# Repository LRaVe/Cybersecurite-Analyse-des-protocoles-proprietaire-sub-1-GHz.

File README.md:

# Projet 2A -  Cybersecurite-Analyse-des-protocoles-proprietaire-sub-1-GHz

## Description du Projet
Bienvenue sur le dépôt GitHub de notre projet de cybersécurité, réalisé dans le cadre de notre projet de deuxième année. Ce projet repose sur l'utilisation du flipper zero, et ensuite de le reproduire avec une STM32WL55.

## Équipe du Projet
Nous sommes une équipe de cinq étudiants :

- **Lucas Raveloarinoro**
- **Hevisinda Top**
- **Wassim Makni**
- **Awa Fofana**
- **Elhoussaine Assanfe**

## Objectifs : 4 Démonstrations et une application

Démo A : Flipper Zero — attaque simple (sans chiffrement) sur la sonnette.

Démo B : Flipper Zero — tentative d’attaque sur la clé de voiture (rolling‑code).

Démo C : STM32WL55 — reproduction de l’attaque simple (sonnette).

Démo D : STM32WL55 — expérimentation et analyse du rolling‑code (clé de voiture).

- La création d’une application sur Flipper capable passivement d’écouter les communications, et en déduire les faiblesses de sécurités des appareils écoutés.

## Organisation du Projet

Afin d’assurer une conduite de projet structurée et efficace, plusieurs outils de planification, de suivi et de conception ont été utilisés tout au long du projet. Ces documents ont permis de clarifier les objectifs, de répartir les tâches et de suivre l’avancement des travaux.

### Planning et gestion du temps
- [Gantt](Organisation/Gantt.png) : planification des différentes phases du projet.  
- [Roadmap](Organisation/Roadmap.png) : suivi de l’avancement au sein de l’équipe.

### Conception et spécification
- [Diagramme des exigences](Organisation/Diagramme_des_Exigences.png) : définition des besoins fonctionnels et techniques du projet.  
- [Cahier des charges](Organisation/Cahier_Des_charges.png) : description des objectifs.

### RSE et Durabilité

Dans le cadre de ce projet, nous avons mené une réflexion sur des thématiques **environnementales et sociétales** :  

- **Durabilité des composants** : nous avons choisi des composants durables et à longue durée de vie pour réduire l’impact environnemental.  
- **Économie d’énergie** : les dispositifs peuvent fonctionner en mode basse consommation afin de limiter la consommation globale.  
- **Impact sociétal** : en analysant les protocoles Sub‑GHz, nous avons également pris en compte l’aspect sécurité et confidentialité des communications.

Ces critères sont **formalisés dans le [Cahier des charges](Organisation/Cahier_Des_charges.png)** et représentés dans le **[Diagramme des exigences](Organisation/Diagramme_des_Exigences.png)**.

## Sous-Projet FlipperZero Application

Rappel Objectif : utiliser les composants inclus dans le FlipperZero pour reconsrtruire du début une application de capture et de relecture de signaux sub-GHz.

### Avancée Dec. 2025 

L'application parvient à récupérer des paquets envoyés de fréquence $\textbf{433.92\~ MHz}$. Il ne manque maintenant que la partie relecture, même s'il est possible de le récupérer directement dans les fichiers du flipper.

### Avancée Jan. 2026 - Application Fonctionnelle ✅

L'application est maintenant **complètement fonctionnelle** avec capture et replay de signaux radio.

#### Architecture de l'Application

```
┌─────────────────────────────────────────────────────────────┐
│                    APPLICATION SUBGHZ                       │
├─────────────────────────────────────────────────────────────┤
│  CAPTURE (app_state=0)                                      │
│  └── furi_hal_subghz_start_async_rx() → capture_callback()  │
│      └── Filtrage du bruit → Stockage dans raw_buffer[]     │
│                                                             │
│  AFFICHAGE (app_state=1)                                    │
│  └── Lecture du fichier .sub sauvegardé                     │
│                                                             │
│  REPLAY (app_state=2)                                       │
│  └── Transmission manuelle TX/IDLE avec timings précis      │
└─────────────────────────────────────────────────────────────┘
```

#### APIs Flipper Zero Utilisées

| API | Fonction |
|-----|----------|
| `furi_hal_subghz_*` | Contrôle du module radio CC1101 (433.92 MHz) |
| `furi_hal_subghz_start_async_rx()` | Démarrage de la capture asynchrone |
| `furi_hal_subghz_tx()` / `furi_hal_subghz_idle()` | Émission/arrêt pour le replay |
| `furi_thread_*` | Threads pour capture/replay non-bloquants |
| `storage_*` / `stream_*` | Lecture/écriture fichiers .sub sur SD |
| `gui_*` / `canvas_*` | Interface utilisateur |

#### Problèmes Rencontrés et Solutions

##### 1. Capture de bruit en permanence
**Problème** : L'antenne capte énormément de bruit électromagnétique ambiant, rendant impossible la distinction d'un vrai signal.

**Solution** : Filtrage multi-niveaux dans `capture_callback()` :
```c
// Ignorer les durées < 150µs (bruit haute fréquence)
if(duration < 150) return;

// Ignorer les durées > 20ms (silence/pause)
if(duration > 20000) return;

// Attendre 30 impulsions valides consécutives avant d'enregistrer
if(consecutive_pulses < 30) return;
```

##### 2. API `subghz_devices` non fonctionnelle
**Problème** : L'API `subghz_devices` (plus récente) causait des blocages - l'appareil ne trouvait pas le device radio.

**Solution** : Utilisation de l'API bas niveau `furi_hal_subghz` qui fonctionne directement avec le CC1101 :
```c
furi_hal_subghz_reset();
furi_hal_subghz_idle();
furi_hal_subghz_load_custom_preset(subghz_device_cc1101_preset_ook_650khz_async_regs);
furi_hal_subghz_set_frequency_and_path(433920000);
```

##### 3. Crash lors du replay avec `async_tx`
**Problème** : L'utilisation de `furi_hal_subghz_start_async_tx()` avec un callback provoquait des crashes (contexte d'interruption incompatible avec certaines fonctions).

**Solution** : Transmission manuelle en alternant `tx()` et `idle()` avec des délais précis :
```c
for(size_t i = 0; i < tx_buffer_size; i++) {
    if(timing > 0) {
        furi_hal_subghz_tx();      // Émet
    } else {
        furi_hal_subghz_idle();    // Silence
    }
    furi_delay_us(abs(timing));    // Attend la durée exacte
}
```

##### 4. UI bloquée sur "ENVOI EN COURS"
**Problème** : Après la transmission, l'écran restait bloqué et n'affichait jamais "TERMINÉ".

**Cause** : L'appel `furi_hal_subghz_sleep()` bloquait indéfiniment le thread.

**Solution** : Suppression de `furi_hal_subghz_sleep()` - la radio reste en mode `idle` ce qui est suffisant.

##### 5. Synchronisation des flags entre threads
**Problème** : Les variables `is_replaying` et `replay_finished` n'étaient pas toujours visibles entre le thread de replay et le thread principal (UI).

**Solution** : Utilisation de `volatile` pour les variables partagées :
```c
volatile bool is_replaying;
volatile bool replay_finished;
```

#### Format du Fichier .sub

```
Filetype: Flipper SubGhz RAW File
Version: 1
Frequency: 433920000
Preset: FuriHalSubGhzPresetOok650Async
Protocol: RAW
RAW_Data: 1001 -352 379 -986 353 -10750 385 -954 999 -350 ...
RAW_Data: 379 -966 1007 -366 987 -368 987 -366 353 -984 ...
```

- **Valeurs positives** : durée HIGH (émission) en µs
- **Valeurs négatives** : durée LOW (silence) en µs

## Sous-Projet STM32

### Objectif

L’objectif de ce sous‑projet est de reproduire, à l’aide d’une carte STM32WL55JC2, le comportement radio observé avec le Flipper Zero.
Cette approche vise à mieux comprendre les communications Sub‑GHz et à évaluer les possibilités d’attaque sur des dispositifs simples, comme une sonnette sans fil à 433 MHz.

La STM32WL55 intègre un module de communciation radio Sub‑GHz, couramment utilisé dans des applications IoT à faible consommation (capteurs, télémétrie, réseaux longue portée). Elle supporte principalement les modulations LoRa et FSK.

### Mise en place de la communication Sub-GHz  
*(Adaptation de l'exemple PingPong)*

Dans un premier temps, une communication radio simple a été mise en place entre deux cartes STM32 à partir de l’exemple Ping‑Pong fourni par ST.
Une carte agit comme émetteur et envoie un message, tandis que l’autre joue le rôle de récepteur et renvoie une réponse. Cette méthode permet de valider le bon fonctionnement de la transmission et de la réception radio, ainsi que la stabilité de la liaison.

La communication a ensuite été contrôlée à l’aide des boutons présents sur les cartes.

Pour la carte correspondant au **Flipper Zero** :

- **Bouton 2** : envoi du signal radio stocké  
- **Bouton 1** : réception et stockage d’un signal radio  

Plusieurs scénarios ont été testés en alternant les rôles des cartes afin de vérifier que l’émission et la réception fonctionnent correctement dans les deux sens. Ces tests ont permis de confirmer que la communication Sub-GHz entre deux STM32 est opérationnelle avec les modulations supportées. 

Une fois cette étape validée, nous avons implémenté un schéma de fonctionnement proche de celui du Flipper Zero : une carte agit comme récepteur‑enregistreur du signal, tandis que la seconde assure l’émission contrôlée d’un signal de test.

### Schéma de principe

```text
┌──────────────────────────────┐      ┌────────────────────────────────┐
│  Carte STM32WL (Émetteur)    │      │  Carte STM32WL (Flipper Zero)   │
│        Carte Test            │<────>│                                │
│                              │      │                                │
│  ComPort <────────────────── │      │ ───────────────────> ComPort   │
└──────────────────────────────┘      └────────────────────────────────┘
```

### Tentative de hacking d’une sonnette 433 MHz

Dans un second temps, nous avons cherché à hacker une sonnette sans fil fonctionnant à 433 MHz, dans l’objectif de reproduire un cas d’attaque similaire à ceux réalisables avec le Flipper Zero. Bien que la fréquence utilisée par la sonnette soit identique à celle exploitée par la carte STM32, aucun signal exploitable n’a pu être reçu.

Cette limitation s’explique par une différence de modulation. La sonnette utilise une modulation de type **ASK/OOK**, tandis que le récepteur Sub-GHz intégré à la STM32 ne prend en charge que les modulations **LoRa** et **FSK**. Ainsi, même avec une fréquence porteuse identique, la modulation incompatible empêche toute réception ou décodage du signal.

### Limites de l’approche STM32

Cette expérimentation met en évidence une limite importante de notre approche : la fréquence seule ne suffit pas pour intercepter ou reproduire un signal radio. Le type de modulation joue un rôle déterminant dans la compatibilité des systèmes.

Contrairement au Flipper Zero, qui supporte un large éventail de modulations grâce à son transceiver dédié, la carte STM32 utilisée reste limitée aux modulations prévues par son matériel.

### PCB Interface homme-machine
Pour reproduire fidèlement le Flipper Zero, nous avons développé une carte PCB de type interface homme-machine (IHM),Prenant la forme d'un shield Arduino (R3) qui s'emboîte parfaitement sur notre carte Nucleo, elle intègre un écran OLED clair et deux boutons de navigation. C'est cette interface simple et robuste qui nous permet de contrôler manuellement l'application radio : capturer un signal, l'enregistrer, et de le retransmettre d'une simple pression. L'ensemble a été conçu pour être stable et fiable, avec une électronique adaptée, afin de se concentrer sur l'objectif du projet.

### Conclusion à mi-durée du sous-projet STM32

En conclusion, nous avons réussi à reproduire partiellement le comportement du Flipper Zero en mettant en place une communication Sub-GHz fonctionnelle entre deux cartes STM32. En revanche, le hacking de la sonnette 433 MHz n’a pas été possible en raison des contraintes matérielles liées aux modulations supportées, ce qui souligne l’importance du choix du transceiver dans les attaques radio Sub-GHz.

## Suite du projet : CaribouLite & Réseaux LoRa sécurisés

Afin de dépasser les limitations rencontrées avec la STM32WL55, nous avons poursuivi le projet en utilisant une plateforme radio beaucoup plus flexible : **CaribouLite sur Raspberry Pi**.  
Cette nouvelle étape nous a permis de revenir à l’écoute large bande Sub-GHz et d’élargir nos capacités d’analyse radio.

Grâce à CaribouLite, nous avons pu :

- observer le spectre radio Sub-GHz de manière plus fine  
- capturer et analyser différents signaux radio  
- confirmer expérimentalement les limites des attaques de replay  

L'étude se fait sur un réseau **Meshtastic**, un système de communication LoRa mesh open-source.

---

## Nouvel objectif : reproduction d’une attaque Man-in-the-Middle

L'objectif est de reproduire une **attaque Man-in-the-Middle (MITM)** sur un réseau radio LoRa.

Une attaque Man-in-the-Middle consiste pour un attaquant à s’interposer entre deux appareils qui communiquent sans qu’ils s’en rendent compte.

Dans ce scénario, l’attaquant peut :
- intercepter les messages échangés
- tenter d’en comprendre le contenu
- modifier les messages avant retransmission
- se faire passer pour l’un des participants

Communication normale :

Appareil A ─────────────► Appareil B

Communication sous attaque MITM :

Appareil A ───► Attaquant ───► Appareil B

Les deux appareils pensent communiquer directement, alors que toute la communication passe en réalité par l’attaquant.

---

La mise en place et les détails du projet sont disponibles dans le dossier :

[LoRa_Meshtastic](LoRa_Meshtastic/README.md)

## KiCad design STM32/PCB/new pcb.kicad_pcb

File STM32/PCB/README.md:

Ce projet consiste en la conception d'un shield au format Arduino R3 pour la carte STM32 Nucleo-WL55JC2. 
Il permet l'affichage d'informations sur un écran OLED et le contrôle manuel de fonctions de lecture/sauvegarde (Rx) et d'émission (Tx) via deux boutons poussoirs.
##  Spécifications Matérielles
Microcontrôleur cible : STM32 Nucleo-WL55JC2 (Logique $3.3 \text{ V}$).
Affichage : Écran OLED SSD1315 via connecteur J5 (7 pins).
Protocole d'affichage : SPI (plus rapide que l'I2C pour les animations).
Contrôles : 2x Boutons poussoirs tactiles avec résistances de rappel externes.
## Logique des Boutons (Active High)
Ce projet utilise des résistances Pull-Down externes pour garantir une immunité au bruit maximale et un signal stable, plus fiable de les configurées.

Composant >  S1 (Read), Valeur > N/A, Fonction > Déclenche la lecture (Rx),État au repos > LOW (0 V), État pressé > HIGH (3.3 V)

Composant >S2 (Send), Valeur > N/A, Fonction > Déclenche l'émission (Tx),État au repos > LOW (0 V), État pressé > HIGH (3.3 V)

Composant > "R1, R2", Valeur > 10 kΩ, Fonction > Résistances Pull-Down,État au repos > Maintenir le signal à 0 V, État pressé > N/A
## Alimentation
Le shield est alimenté par le rail $+3V3$ de la Nucleo.Les boutons tirent leur alimentation en parallèle de la ligne de l'écran OLED pour simplifier le routage.
> L'utilisation du $+5 \text{ V}$ est strictement interdite pour éviter d'endommager les GPIO du STM32.
## Brochage (Pinout)
Signal > BTN_RX (S1),Pin Shield (Arduino) > D2,Pin STM32 (Nucleo) > PA10

Signal > BTN_TX (S2),Pin Shield (Arduino) > D3,Pin STM32 (Nucleo) > PB3

Signal > OLED_CS,Pin Shield (Arduino) > D10,Pin STM32 (Nucleo) > PA4

Signal > SPI_MOSI,Pin Shield (Arduino) > D11,Pin STM32 (Nucleo) > PA7

Signal > SPI_SCK,Pin Shield (Arduino) > D13,Pin STM32 (Nucleo) > PA5

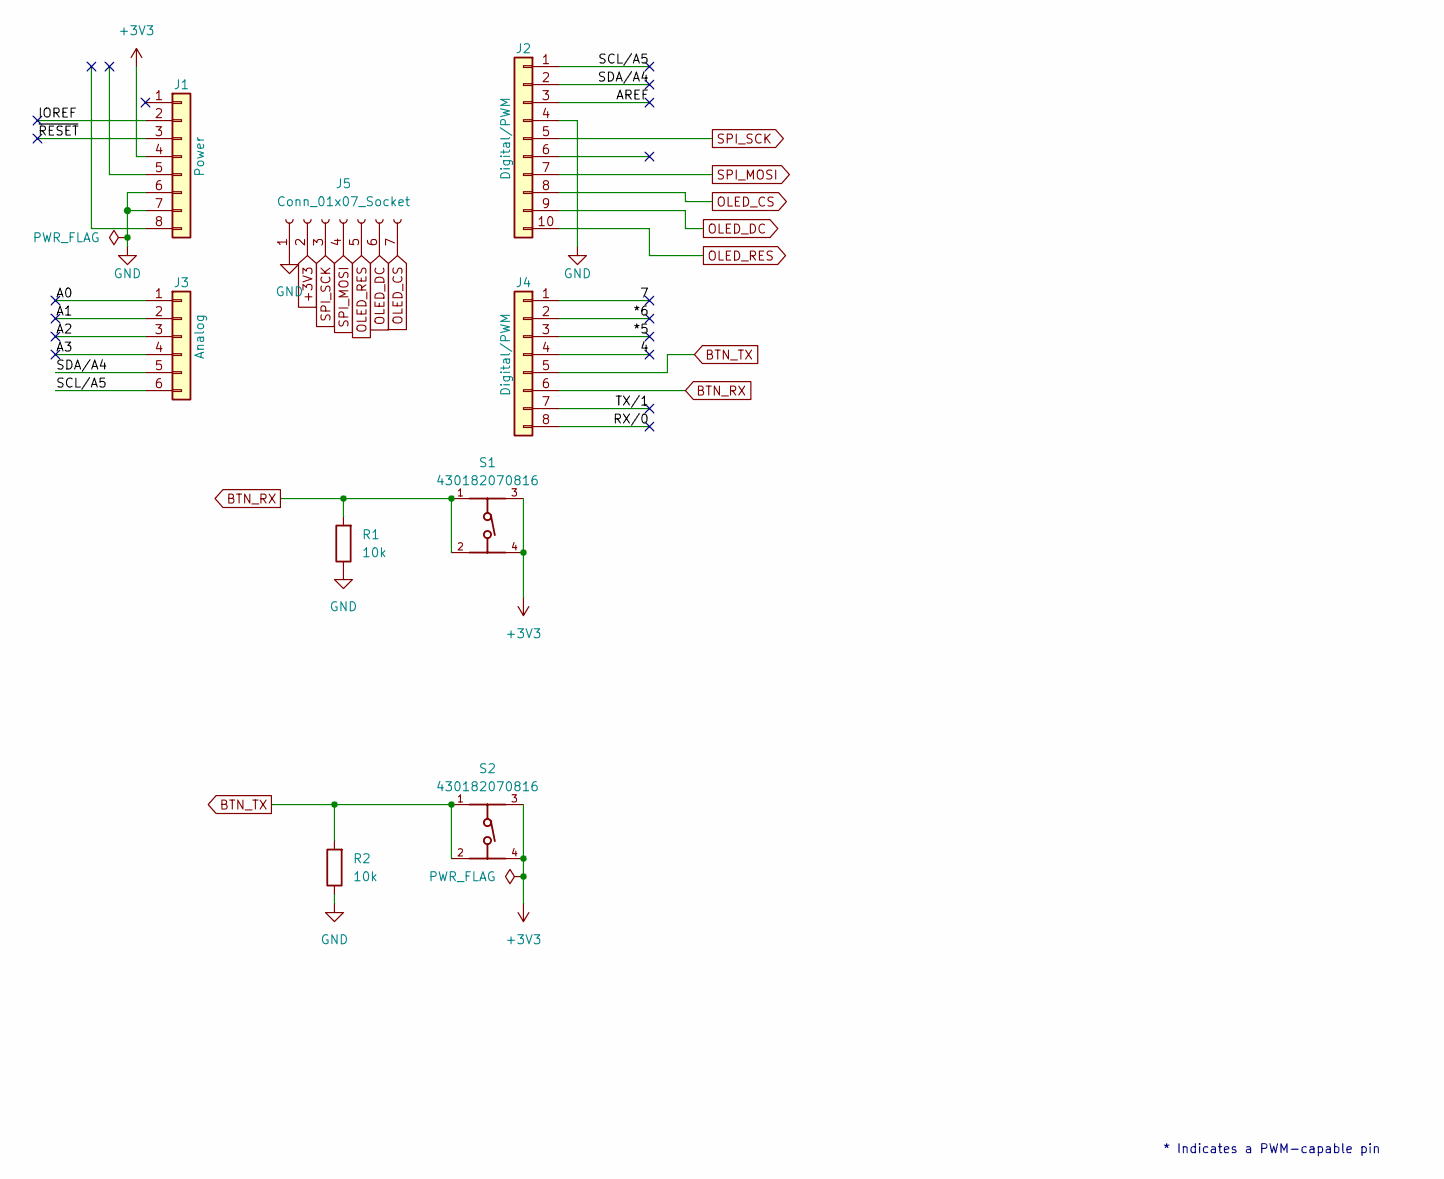
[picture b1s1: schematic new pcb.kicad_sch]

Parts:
J1: Power; PinSocket_1x08_P2.54mm_Vertical
J2: Digital/PWM; PinSocket_1x10_P2.54mm_Vertical
J3: Analog; PinSocket_1x06_P2.54mm_Vertical
J4: Digital/PWM; PinSocket_1x08_P2.54mm_Vertical
J5: Conn_01x07_Socket; PinSocket_1x07_P2.54mm_Vertical
R1, R2: 10k; R_0805_2012Metric_Pad1.20x1.40mm_HandSolder
S1, S2: 430182070816

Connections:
+3V3: J1.4, J5.2, S1.3, S1.4, S2.3, S2.4
/4: J4.4
/7: J4.1
/12: J2.6
/*5: J4.3
/*6: J4.2
/A0: J3.1
/A1: J3.2
/A2: J3.3
/A3: J3.4
/AREF: J2.3
/IOREF: J1.2
/RX/0: J4.8
/SCL/A5: J2.1, J3.6
/SDA/A4: J2.2, J3.5
/TX/1: J4.7
/~RESET: J1.3
BTN_RX: J4.6, R1.2, S1.1, S1.2
BTN_TX: J4.5, R2.2, S2.1, S2.2
GND: J1.6, J1.7, J2.4, J5.1, R1.1, R2.1
OLED_CS: J2.8, J5.7
OLED_DC: J2.9, J5.6
OLED_RES: J2.10, J5.5
SPI_MOSI: J2.7, J5.4
SPI_SCK: J2.5, J5.3

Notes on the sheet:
* Indicates a PWM-capable pin

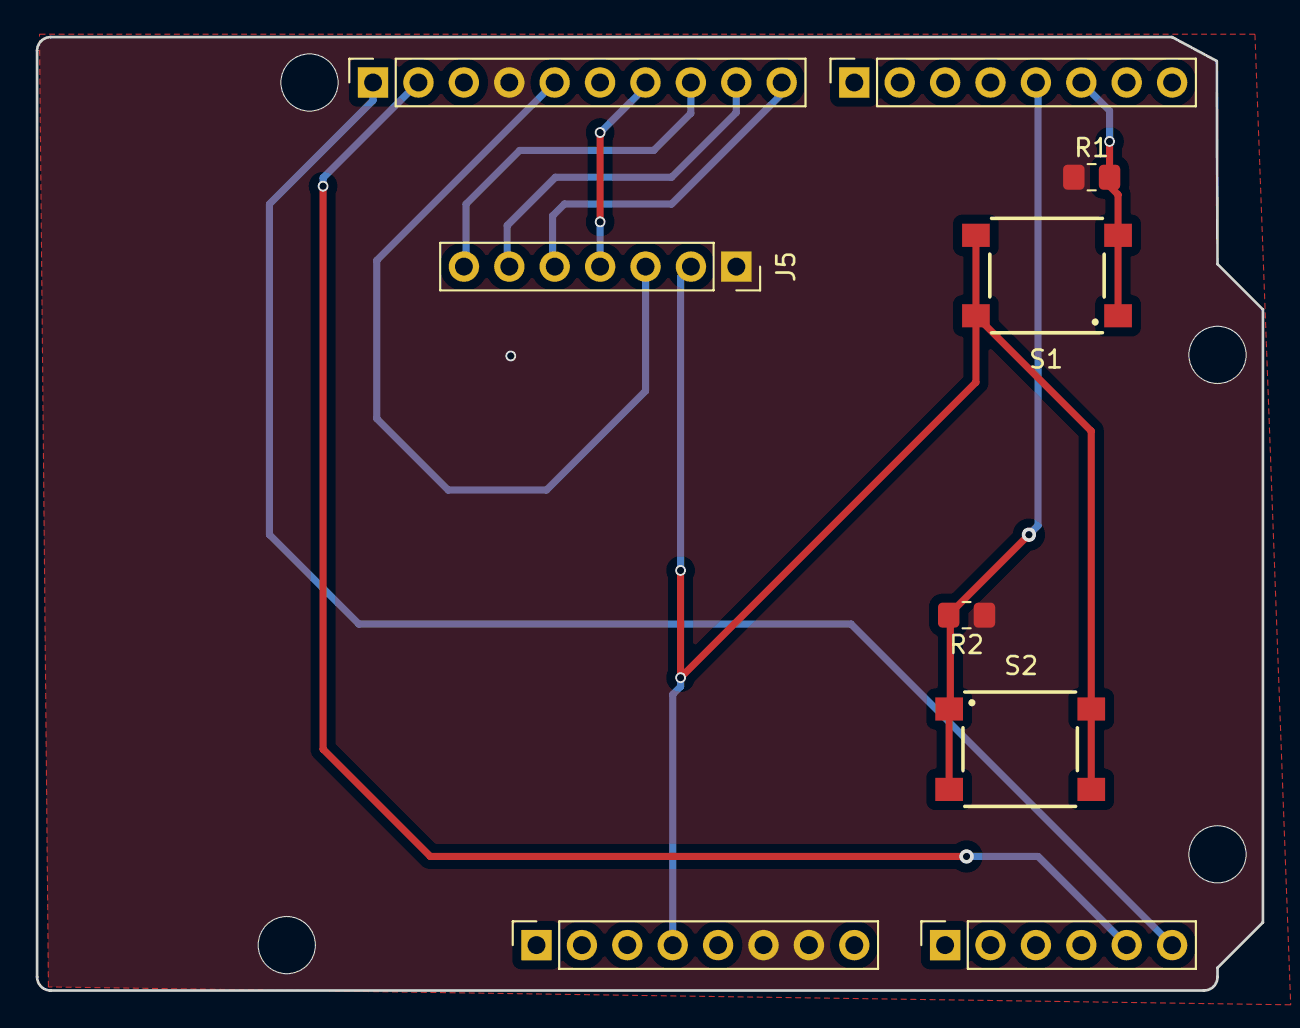
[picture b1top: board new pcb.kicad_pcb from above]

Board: 2 copper layers, 68.6 x 53.3 mm, 13 parts (0 on the bottom side), 11 nets.

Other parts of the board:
MH1, MH2, MH3, MH4: MountingHole_3.2mm

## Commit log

2025-09-16 Create To do list
2025-09-23 Update To do list
2025-10-21 Create Datasheet Folder
2025-12-16 FlipperZero App First commit
2025-12-16 ReadMe updated
2026-01-06 Application ver.1 terminée
2026-01-06 Create file
2026-01-06 Application fonctionnelle (à part peut-être le replay mais c'est gérable autrement)
2026-01-06 README terrifiant-
2026-01-13 Add temp directory under STM32/PCB
2026-01-13 Update README for clarity and formatting improvements
2026-01-13 Add first rolling code program for Flipper Zero
2026-01-13 Add rolljam app 1st. ver.
2026-01-13 Create tes
2026-01-13 Move sub_ghz_app.c to sub_ghz_app/sub_ghz_app.c
2026-01-13 Move application.fam to sub_ghz_app/application.fam
2026-01-13 Move sub_ghz_app.png to sub_ghz_app/sub_ghz_app.png
2026-01-13 Move files
2026-01-13 Separate workflow builds of the two applications
2026-01-13 Fix GitHub Actions: add app-dir for subfolder structure
2026-01-13 Add README for STM32 Nucleo-WL55JC2 shield project
    This README provides an overview of the Arduino R3 shield project for the STM32 Nucleo-WL55JC2, including specifications, button logic, power supply details, and pinout information.
2026-01-13 Enhance README formatting and content clarity
    Updated the README to improve clarity and formatting, including tables for button logic and pin assignments.
2026-01-13 Revise README for button controls and pull-down resistors
    Updated button functionality descriptions and improved clarity on pull-down resistor usage.
2026-01-13 Improve formatting of README.md
    Updated the README to improve formatting and clarity.
2026-01-13 Add PCB interface section to README
    Added a section about the PCB human-machine interface, detailing its features and purpose.
2026-01-13 Restore PCB Interface section in README
    Restored PCB interface section in README and clarified its purpose.
2026-02-17 README update
2026-04-16 Create test
2026-04-16 Revise README for Meshtastic project details
    Updated project description for clarity and focus.
